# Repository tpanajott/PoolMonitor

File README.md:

# PoolMonitor

<!-- @import "[TOC]" {cmd="toc" depthFrom=1 depthTo=6 orderedList=false} -->

<!-- code_chunk_output -->

- [PoolMonitor](#poolmonitor)
  - [Description](#description)
  - [Hardware](#hardware)
    - [PCB Manufacturing](#pcb-manufacturing)
    - [Parts](#parts)
    - [Sensor](#sensor)
    - [Jumpers](#jumpers)
      - [Disable pol prot](#disable-pol-prot)
      - [Disable power ctrl](#disable-power-ctrl)
  - [Installation of software](#installation-of-software)
  - [Home Assistant configuration](#home-assistant-configuration)

<!-- /code_chunk_output -->

## Description
This is a small PCB made to monitor the temperature of a pool using a DS18B20 waterproof sensor. The PCB is based around a ESP-12 module that will connect to WiFi periodically (period time configurable) and report the temperature together with battery voltage via MQTT. In between the meassurements, the sensors are turned off to save battery.

## Hardware
### PCB Manufacturing
I had the board manufactured at [JLCPCB](https://jlcpcb.com/). Simply upload the ZIP-file in the `PCB/gerbers` directory to their website. The following PCB stackup is used:
|Layer|Name|
|---|---|
|L1(Top Layer)|PoolMonitor-F_Cu.gtl|
|L2(Inner Layer1)|PoolMonitor-GND.g2|
|L3(Inner Layer2)|PoolMonitor-3_3V.g3|
|L4(Bottom Layer)|PoolMonitor-B_Cu.gbl|

### Parts
A BOM for the project is available in the file `PCB/PoolMonitor.csv`. The parts list have references to [LCSC](https://lcsc.com/) part numbers.

### Sensor
This board is designed to use a simple DS18B20 sensor with three wires. The following wiring diagram is to be used and the sensor should be connected to the `TempSense1` connector.
|Wire Color|Connection|
|---|---|
|Red|+|
|Black|-|
|Yellow|D|

### Jumpers
#### Disable pol prot
This jumber, when briged, will disable the polarity protection on the power input.
#### Disable power ctrl
This jumber will, when briged, disable to power control of the DS18B20 sensor when not reading from it. By default the power to the DS18B20 sensor will only be turned on while reading data from it in an attempt to conserve power.

## Installation of software
1. Connect a FTDI programmer set to 3.3V to the header on the PCB.
2. Download and installation VS Code together with the PlatformIO extention.
3. Download this repo and open it with PlatformIO.
4. Hold the SW_FLASH1 button and press and release the SW_RESET1 button. This will put the device into a programming mode.
5. Create a copy of the "settings.h.example" file found in the "src/" directory and name it `settings.h`.
6. Configure all relevant paramaters in the `settings.h` file.
7. Make sure to save everything and then press "Upload" in PlatformIO.
8. Once the upload is complete, disconnect the FTDI-programmer.
9. Done, enjoy.

## Home Assistant configuration
The following configuration example can be added to the `sensor` section in your Home Assistant configuration. The `expire_after` paramater set to 4200 means that Home Assistant will consider the value old if 70 minutes has passed since last update from sensor. This value may need to be changed in order to reflect your configuration of the `SLEEP_TIME` paramater in the `settings.h` file.
```yaml
- platform: mqtt
  device_class: temperature
  name: "Pool temperature"
  state_topic: "/pool/temp/"
  unit_of_measurement: "°C"
  expire_after: 4200
- platform: mqtt
  device_class: temperature
  name: "Pool sensor voltage"
  state_topic: "/pool/voltage/"
  unit_of_measurement: "V"
  expire_after: 4200
```

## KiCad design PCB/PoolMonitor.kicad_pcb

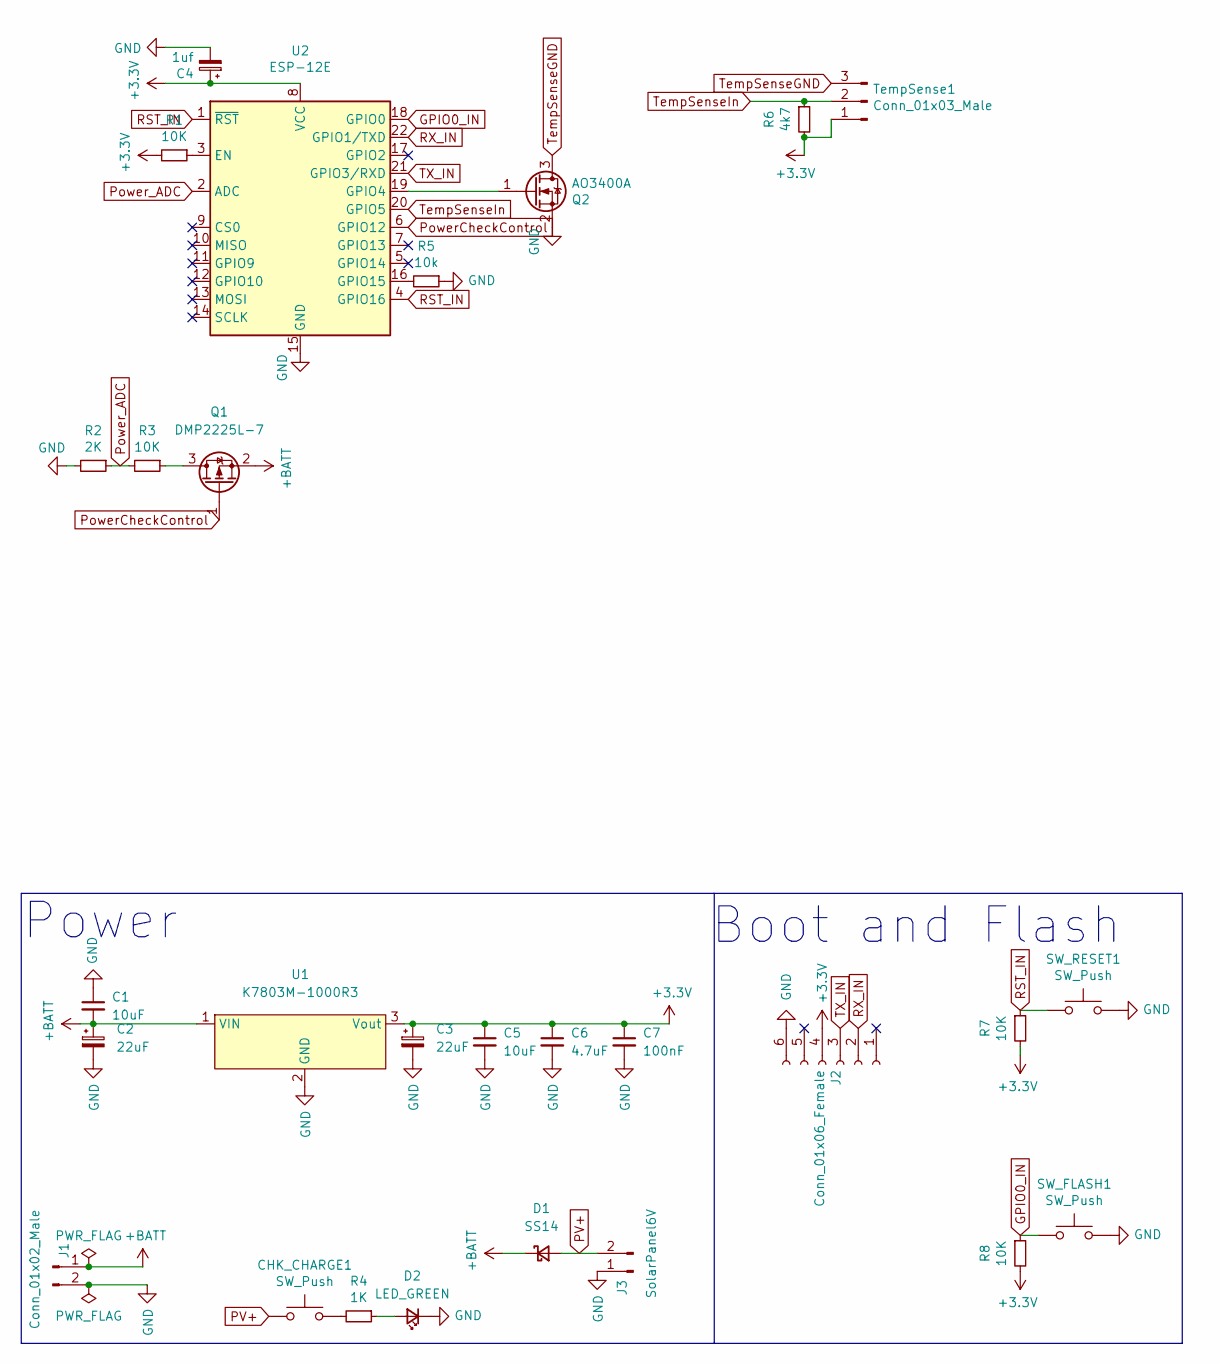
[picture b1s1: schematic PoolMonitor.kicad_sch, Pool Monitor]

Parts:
C1, C5: 10uF; C_0805_2012Metric; LCSC C440198
C2, C3: 22uF; CP_Radial_D5.0mm_P2.00mm; LCSC C89789
C4: 1uf; C_0603_1608Metric; LCSC C92828
C6: 4.7uF; C_1206_3216Metric; LCSC C132170
C7: 100nF; C_0805_2012Metric; LCSC C49678
CHK_CHARGE1: SW_Push; SW_Push_SPST_NO_Alps_SKRK; LCSC C115357
D1: SS14; D_SMA; LCSC C2837270
D2: LED_GREEN; LED_1206_3216Metric; LCSC C125085
J1: Conn_01x02_Male; JST_PH_B2B-PH-K_1x02_P2.00mm_Vertical; LCSC C131337
J2: Conn_01x06_Female; PinSocket_1x06_P2.54mm_Vertical; LCSC C225503
J3: SolarPanel6V; JST_PH_B2B-PH-K_1x02_P2.00mm_Vertical; LCSC C131337
Q1: DMP2225L-7; SOT-23; LCSC C110501
Q2: AO3400A; SOT-23; LCSC C344010
R1, R3, R7, R8: 10K; R_0603_1608Metric; LCSC C98220
R2: 2K; R_0603_1608Metric; LCSC C22975
R4: 1K; R_1206_3216Metric
R5: 10k; R_0603_1608Metric; LCSC C98220
R6: 4k7; R_1206_3216Metric_Pad1.30x1.75mm_HandSolder; LCSC C242482
SW_FLASH1: SW_Push; SW_Push_SPST_NO_Alps_SKRK; LCSC C115357
SW_RESET1: SW_Push; SW_Push_SPST_NO_Alps_SKRK; LCSC C115357
TempSense1: Conn_01x03_Male; JST_PH_B3B-PH-K_1x03_P2.00mm_Vertical; LCSC C131339
U1: K7803M-1000R3; CONV_K7803M-1000R3; LCSC C494983
U2: ESP-12E; LCSC C89297

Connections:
+3V3: C3.1, C4.1, C5.1, C6.1, C7.1, J2.4, R1.2, R6.2, R7.2, R8.2, TempSense1.1, U1.3 (Vout), U2.8 (VCC)
+BATT: C1.2, C2.1, D1.1 (K), J1.1, Q1.2 (S), U1.1 (VIN)
GND: C1.1, C2.2, C3.2, C4.2, C5.2, C6.2, C7.2, D2.1 (K), J1.2, J2.6, J3.1, Q2.2 (S), R2.2, R5.1, SW_FLASH1.2, SW_RESET1.2, U1.2 (GND), U2.15 (GND)
GPIO0_IN: R8.1, SW_FLASH1.1, U2.18 (GPIO0)
unnamed: CHK_CHARGE1.2, R4.2
unnamed: D2.2 (A), R4.1
unnamed: Q1.3 (D), R3.1
unnamed: Q2.1 (G), U2.19 (GPIO4)
unnamed: R1.1, U2.3 (EN)
unnamed: R5.2, U2.16 (GPIO15)
PV+: CHK_CHARGE1.1, D1.2 (A), J3.2
PowerCheckControl: Q1.1 (G), U2.6 (GPIO12)
Power_ADC: R2.1, R3.2, U2.2 (ADC)
RST_IN: R7.1, SW_RESET1.1, U2.1 (~RST), U2.4 (GPIO16)
RX_IN: J2.2, U2.22 (GPIO1/TXD)
TX_IN: J2.3, U2.21 (GPIO3/RXD)
TempSenseGND: Q2.3 (D), TempSense1.3
TempSenseIn: R6.1, TempSense1.2, U2.20 (GPIO5)

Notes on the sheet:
Power
Boot and Flash

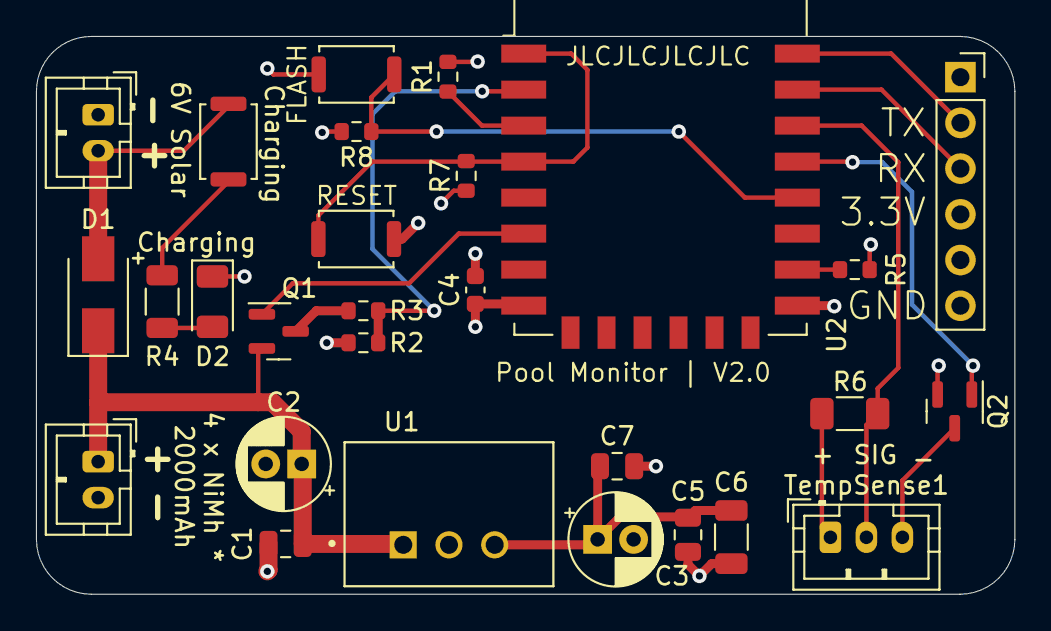
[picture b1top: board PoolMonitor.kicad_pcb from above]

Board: 4 copper layers, 54.4 x 31.0 mm, 28 parts (0 on the bottom side), 18 nets.

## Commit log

2022-01-17 Added README
2022-01-17 First commit of PCB and code
2022-01-17 Updated README with instructions for how to install the software
2022-06-14 Updated PCB and software to be able to read battery voltage as well as added solar charging capabilities to PCB
2022-06-14 Updated to use all JST connectors and updated REAME with a description
2022-06-14 Removed designators as they were not needed
2022-06-14 Updated image
2022-06-24 Added workaround for errenious readings every once in a while. If a readins is below -100C, try again up to three times
2022-07-03 Implemented fix for sometimes not getting a reading from the sensor
